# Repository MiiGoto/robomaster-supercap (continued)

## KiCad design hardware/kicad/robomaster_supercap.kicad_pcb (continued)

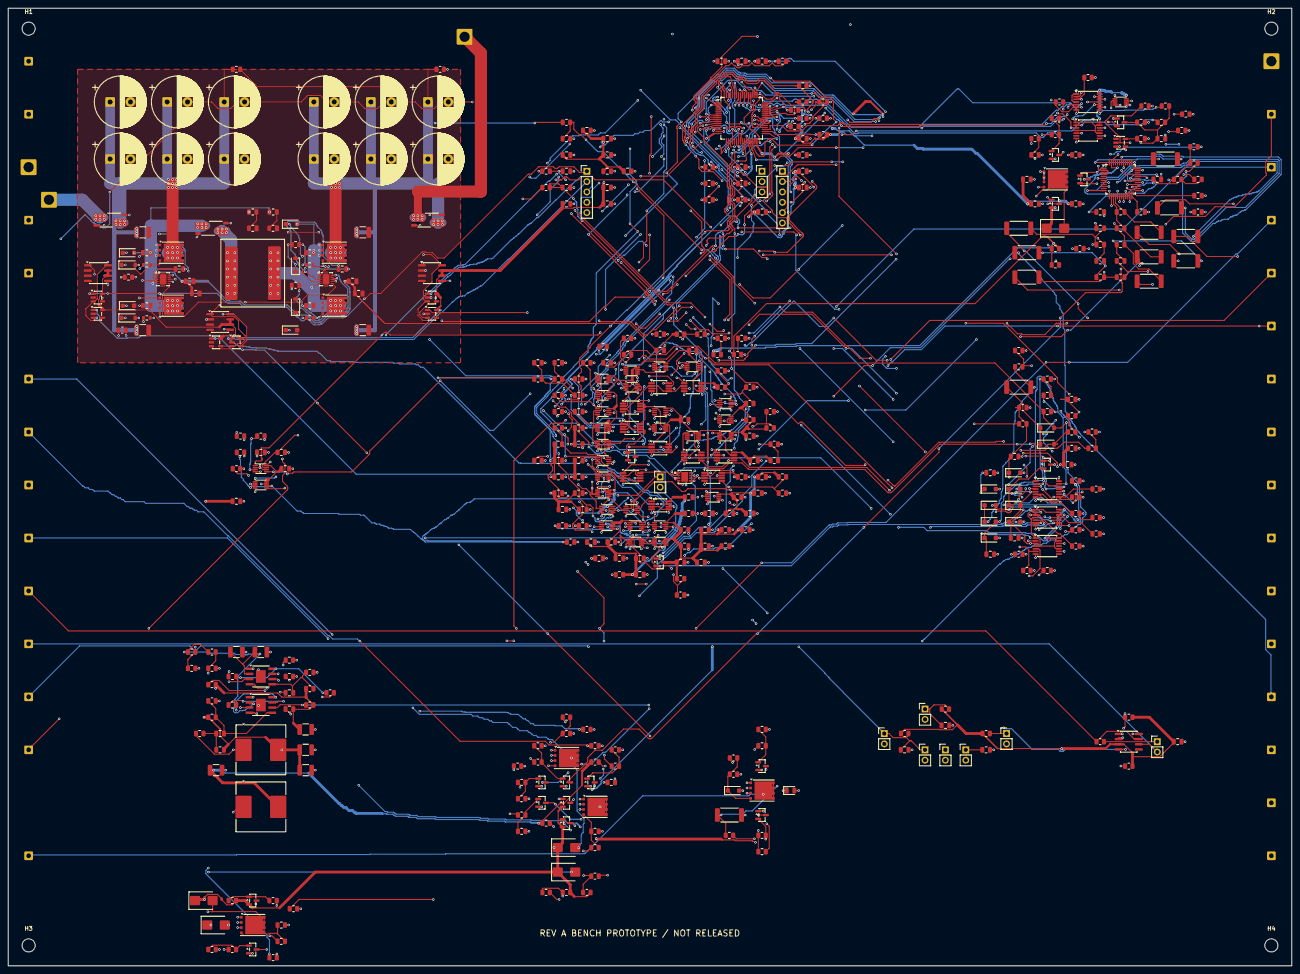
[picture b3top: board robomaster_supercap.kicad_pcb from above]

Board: 4 copper layers, 315.0 x 235.0 mm, 485 parts (0 on the bottom side), 285 nets.

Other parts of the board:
H1, H2, H3, H4: MountingHole_3.2mm_M3

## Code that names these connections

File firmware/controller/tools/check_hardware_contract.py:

"""Read-only audit against a native KiCad S-expression netlist export.

Usage: python -B check_hardware_contract.py path/to/rev_a.net
Export is local-only: it may contain private absolute paths and is not committed.
"""
import sys
from pathlib import Path

ROOT = Path(__file__).resolve().parents[3]
sys.path.insert(0, str(ROOT / "tools"))
from read_kicad import parse, child, children

# Physical LQFP64 pad, GPIO, electrical net; reviewed from U11 and datasheet.
CONTRACT = """
24 PB0 ARM_PULSE
25 PB1 WD_HEARTBEAT
26 PB2 MCU_GATE_REQUEST
30 PB10 PRE_BUS_REQUEST
33 PB11 BYP_BUS_REQUEST
38 PC6 BUS_ISO_REQUEST
39 PC7 CAP_ISO_REQUEST
40 PC8 PRE_CAP_REQUEST
41 PC9 BYP_CAP_REQUEST
52 PC10 DUMP_REQUEST
55 PD2 MON_CONFIG_VALID
42 PA8 PWM_AH
43 PA9 PWM_AL
44 PA10 PWM_BH
45 PA11 PWM_BL
46 PA12 HW_FAULT_N
8 PC0 TEMP_FET_ADC
9 PC1 TEMP_L_ADC
10 PC2 TEMP_BANK_ADC
11 PC3 BUS_RAW_ADC
12 PA0 BUS_V_ADC
13 PA1 CAP_V_ADC
18 PA4 BUS_I_ADC
19 PA5 CAP_I_ADC
20 PA6 IL_I_ADC
22 PC4 CAP_RAW_ADC
34 PB12 MON_CS_HOST
35 PB13 MON_SCLK_HOST
36 PB14 MON_MISO_HOST
37 PB15 MON_MOSI_HOST
53 PC11 MON_ALERT_HOST
61 PB8 CAN_RX
62 PB9 CAN_TX
54 PC12 CAN_STANDBY
14 PA2 UART_TX
17 PA3 UART_RX
49 PA13 SWDIO
50 PA14 SWCLK
56 PB3 SWO
2 PC13 PRE_CAP_FB
51 PA15 PRE_BUS_FB
57 PB4 BUS_ISO_FB
58 PB5 CAP_ISO_FB
59 PB6 BYP_BUS_FB
60 PB7 BYP_CAP_FB
23 PC5 REFEREE_PERMIT
7 PG10 NRST
"""

def check(path):
    native = parse(path.read_text(encoding="utf-8"))
    actual = {}
    for net in children(child(native, "nets"), "net"):
        for node in children(net, "node"):
            if child(node, "ref")[1] == "U11":
                actual[child(node, "pin")[1]] = (
                    child(node, "pinfunction")[1].split("_")[0], child(net, "name")[1])
    count = 0
    for row in CONTRACT.splitlines():
        if row.strip():
            pad, pin, name = row.split()
            assert actual.get(pad) == (pin, name), (pad, pin, name, actual.get(pad))
            count += 1
    board = (ROOT / "firmware/controller/Core/Src/board.c").read_text(encoding="utf-8")
    for token in ("GPIO_AF13_HRTIM1", "GPIO_AF5_SPI2", "GPIO_AF9_FDCAN1",
                  "ADC_CHANNEL_17", "ADC_CHANNEL_13", "ADC_REGULAR_RANK_6"):
        assert token in board, token
    print(f"PASS {count} U11 physical pin/net assignments; AF/ADC rank sentinels present")

if __name__ == "__main__":
    check(Path(sys.argv[1]))

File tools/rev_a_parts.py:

"""Original pin tables from manufacturer facts, not copied schematic assets.

Pin electrical types remain explicit for ERC. Package numbers are physical pad
numbers. Footprints are candidates; land dimensions require independent review.
"""
from dataclasses import dataclass

@dataclass
class Part:
    pins: dict
    footprint: str
    source: str = ''

P = {}
def part(name, pins, fp, source=''):
    # 'name:type'; omitted type is passive (R/C/L, contacts, semiconductor terminals).
    P[name] = Part({str(k): tuple(v.split(':')) if ':' in v else (v,'passive')
                    for k,v in pins.items()}, fp, source)

RFP='Resistor_SMD:R_0805_2012Metric'
CFP='Capacitor_SMD:C_0805_2012Metric'
SO8='Package_SO:SOIC-8_3.9x4.9mm_P1.27mm'
VSS8='Package_SO:VSSOP-8_3x3mm_P0.65mm'
DCU8='Package_SO:VSSOP-8_2.3x2mm_P0.5mm'
part('R',{1:'A',2:'B'},RFP)
part('J1_PAD',{1:'WIRE'},'Connector_Wire:SolderWire-0.5sqmm_1x01_D0.9mm_OD2.1mm')
part('C',{1:'A',2:'B'},CFP)
part('L',{1:'A',2:'B'},'Inductor_SMD:L_Coilcraft_XAL1510-223')
part('D',{1:'K',2:'A'},'Diode_SMD:D_SOD-123')
part('LED',{1:'K',2:'A'},'LED_SMD:LED_0805_2012Metric')
part('Q_NPN',{1:'B',2:'E',3:'C'},'Package_TO_SOT_SMD:SOT-23','https://www.nexperia.com/product/BC847B')
part('Q_PNP',{1:'B',2:'E',3:'C'},'Package_TO_SOT_SMD:SOT-23','https://www.nexperia.com/product/BC857B')
part('FUSE',{1:'A',2:'B'},'','https://www.littelfuse.com/assetdocs/littelfuse-datasheet-997-mini58v?assetguid=838cc4ad-f429-4185-a8e8-ccc70cd2b713')
# KiCad functional aliases: 1=S physical1/2/3, 2=G physical4,
# 3=D physical5/6/7/8 and drain metal. See pinout review before layout.
part('CSD18540Q5B',{1:'S_DS1_2_3',2:'G_DS4',3:'D_DS5_6_7_8'},
     'Package_SON:VSONP-8-1EP_5x6_P1.27mm','https://www.ti.com/lit/ds/symlink/csd18540q5b.pdf')
part('UCC27282DRCR',{1:'VDD:power_in',2:'NC:no_connect',3:'HB:passive',4:'HO:output',5:'HS:passive',6:'EN:input',7:'HI:input',8:'LI:input',9:'VSS:power_in',10:'LO:output',11:'EP:power_in'},
     'Package_SON:VSON-10-1EP_3x3mm_P0.5mm_EP1.65x2.4mm','https://www.ti.com/lit/ds/symlink/ucc27282.pdf')
for n in ('INA240A1D','INA240A2D'):
    part(n,{1:'INM:input',2:'GND:power_in',3:'REF2:input',4:'NC:no_connect',5:'OUT:output',6:'VS:power_in',7:'REF1:input',8:'INP:input'},SO8,'https://www.ti.com/lit/ds/symlink/ina240.pdf')
part('WSK25123L000FEA',{1:'I_P',2:'K_P',3:'K_M',4:'I_M'},
     'Resistor_SMD:R_Shunt_Vishay_WSK2512_6332Metric_T2.21mm','https://www.vishay.com/docs/30108/wsk2512.pdf')
part('INA293A1DBVR',{1:'OUT:output',2:'GND:power_in',3:'INP:input',4:'INM:input',5:'VS:power_in'},'Package_TO_SOT_SMD:SOT-23-5','https://www.ti.com/lit/ds/symlink/ina293.pdf')
part('INA301A1DGKR',{1:'VS:power_in',2:'OUT:output',3:'LIMIT:input',4:'GND:power_in',5:'RESET:input',6:'ALERT_N:open_collector',7:'INM:input',8:'INP:input'},VSS8,'https://www.ti.com/lit/ds/symlink/ina301.pdf')
part('TLV3202DGKR',{1:'OUT1:output',2:'INM1:input',3:'INP1:input',4:'GND:power_in',5:'INP2:input',6:'INM2:input',7:'OUT2:output',8:'VCC:power_in'},VSS8,'https://www.ti.com/lit/ds/symlink/tlv3202.pdf')
part('SN74LVC1G74DCUR',{1:'CLK:input',2:'D:input',3:'QN:output',4:'GND:power_in',5:'Q:output',6:'CLR_N:input',7:'PRE_N:input',8:'VCC:power_in'},DCU8,'https://www.ti.com/lit/ds/symlink/sn74lvc1g74.pdf')
part('SN74LVC2G08DCUR',{1:'A1:input',2:'B1:input',3:'Y2:output',4:'GND:power_in',5:'A2:input',6:'B2:input',7:'Y1:output',8:'VCC:power_in'},DCU8,'https://www.ti.com/lit/ds/symlink/sn74lvc2g08.pdf')
part('TPS3431SDRBR',{1:'VDD:power_in',2:'CWD:passive',3:'EN:input',4:'GND:power_in',5:'SET1:input',6:'WDI:input',7:'WDO_N:open_collector',8:'ENOUT:open_collector',9:'EP:power_in'},
     'Package_SON:VSON-8-1EP_3x3mm_P0.65mm_EP1.65x2.4mm','https://www.ti.com/lit/ds/symlink/tps3431.pdf')
part('TPS3839K33DBZR',{1:'GND:power_in',2:'RESET_N:output',3:'VDD:power_in'},'Package_TO_SOT_SMD:SOT-23','https://www.ti.com/lit/ds/symlink/tps3839.pdf')
part('LM5164DDAR',{1:'GND:power_in',2:'VIN:power_in',3:'EN:input',4:'RON:passive',5:'FB:input',6:'PGOOD:open_collector',7:'BST:passive',8:'SW:passive',9:'EP:power_in'},
     'Package_SO:TI_SO-PowerPAD-8','https://www.ti.com/lit/ds/symlink/lm5164.pdf')
part('TMUX1511PWR',{1:'SEL1:input',2:'S1:passive',3:'D1:passive',4:'SEL2:input',5:'S2:passive',6:'D2:passive',7:'GND:power_in',8:'D3:passive',9:'S3:passive',10:'SEL3:input',11:'D4:passive',12:'S4:passive',13:'SEL4:input',14:'VDD:power_in'},
     'Package_SO:TSSOP-14_4.4x5mm_P0.65mm','https://www.ti.com/lit/ds/symlink/tmux1511.pdf')
part('TLV431AIDBZR',{1:'REF:input',2:'K:passive',3:'A:passive'},'Package_TO_SOT_SMD:SOT-23','https://www.ti.com/lit/ds/symlink/tlv431.pdf')
part('SN65HVD230DR',{1:'D:input',2:'GND:power_in',3:'VCC:power_in',4:'R:output',5:'VREF:output',6:'CANL:bidirectional',7:'CANH:bidirectional',8:'RS:input'},SO8,'https://www.ti.com/lit/ds/symlink/sn65hvd230.pdf')
part('SN74LV1T34DBVR',{1:'NC:no_connect',2:'A:input',3:'GND:power_in',4:'Y:output',5:'VCC:power_in'},'Package_TO_SOT_SMD:SOT-23-5','https://www.ti.com/lit/ds/symlink/sn74lv1t34.pdf')
bq={1:'NC',2:'VC9',3:'NC',4:'VC8',5:'NC',6:'VC7',7:'NC',8:'VC6',9:'NC',10:'VC5',11:'NC',12:'VC4',13:'VC3',14:'VC2',15:'VC1',16:'VC0',17:'VSS:power_in',18:'SRP:input',19:'NC',20:'SRN:input',21:'TS1:passive',22:'TS2:passive',23:'TS3:passive',24:'REG18:power_out',25:'ALERT:open_collector',26:'SCLK:input',27:'MISO:output',28:'MOSI:input',29:'CS_N:input',30:'DFETOFF:input',31:'DCHG:output',32:'DDSG:output',33:'RST_SHUT:input',34:'REG2:power_out',35:'REG1:power_out',36:'REGIN:power_in',37:'BREG:output',38:'FUSE:passive',39:'PDSG:output',40:'PCHG:output',41:'LD:passive',42:'PACK:input',43:'DSG:output',44:'NC',45:'CHG:output',46:'CP1:passive',47:'BAT:power_in',48:'VC10:input'}
bq={i:('NC:no_connect' if s=='NC' else s+':input' if s.startswith('VC') and ':' not in s else s) for i,s in bq.items()}
part('BQ7694204PFBR',bq,'Package_QFP:TQFP-48_7x7mm_P0.5mm','https://www.ti.com/lit/ds/symlink/bq76942.pdf')
# LQFP64 physical pin map, DS12288 Rev6 Figure15 / Table12.
mcu_names='VBAT PC13 PC14 PC15 PF0 PF1 PG10 PC0 PC1 PC2 PC3 PA0 PA1 PA2 VSS VDD PA3 PA4 PA5 PA6 PA7 PC4 PC5 PB0 PB1 PB2 VSSA VREF+ VDDA PB10 VSS VDD PB11 PB12 PB13 PB14 PB15 PC6 PC7 PC8 PC9 PA8 PA9 PA10 PA11 PA12 VSS VDD PA13 PA14 PA15 PC10 PC11 PC12 PD2 PB3 PB4 PB5 PB6 PB7 PB8 PB9 VSS VDD'.split()
mcu=dict(enumerate(mcu_names,1))
part('STM32G474RET6',{i:s+(':power_in' if s in ('VBAT','VSS','VDD','VSSA','VDDA','VREF+') else ':bidirectional') for i,s in mcu.items()},
     'Package_QFP:LQFP-64_10x10mm_P0.5mm','https://www.st.com/resource/en/datasheet/stm32g474re.pdf')
for n in (2,3,4,5,6,10):
    part('J'+str(n),{i:'P'+str(i) for i in range(1,n+1)},f'Connector_PinHeader_2.54mm:PinHeader_1x{n:02}_P2.54mm_Vertical')
part('CONTACT',{1:'COM',2:'NO',3:'COIL_P',4:'COIL_M'},'','https://industry.panasonic.com/global/en/products/control/relay/vehicle/number/aev14012')
part('AQZ202G',{1:'LED_M',2:'LED_P',3:'ACDC_A',4:'ACDC_B'},'',
     'https://industry.panasonic.com/ac/cdn/e/control/relay/photomos/catalog/semi_eng_pwr1a_aqz10_20.pdf')
part('DDR60L12',{1:'VO_M',2:'VO_M',3:'VO_P',4:'VO_P',5:'VIN_P',6:'VIN_M'},'',
     'https://www.meanwell.com/Upload/PDF/DDR-60/DDR-60-SPEC.PDF')
part('DISCONNECT',{1:'COM',2:'SWITCHED'},'',
     'https://www.bluesea.com/products/compare/6004/6004200/6005200/6006/6006200')
part('PWR_FLAG',{1:'SUPPLY:power_out'},'')

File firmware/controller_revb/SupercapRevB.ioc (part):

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Mcu.Name=STM32G431C(6-8-B)Tx
Mcu.Package=LQFP48
Mcu.UserName=STM32G431CBTx
PA0.GPIOParameters=GPIO_Label
PA0.GPIO_Label=VNODE_S
PA0.Mode=IN1-Single-Ended
PA0.Signal=ADC1_IN1
PA1.GPIOParameters=GPIO_Label
PA1.GPIO_Label=VINC_S
PA1.Mode=IN2-Single-Ended
PA1.Signal=ADC1_IN2
PA11.Mode=FDCAN_Activate
PA11.Signal=FDCAN1_RX
PA12.Mode=FDCAN_Activate
PA12.Signal=FDCAN1_TX
PA13.Mode=Serial_Wire
PA13.Signal=SYS_JTMS-SWDIO
PA14.Mode=Serial_Wire
PA14.Signal=SYS_JTCK-SWCLK
PA2.GPIOParameters=GPIO_Label
PA2.GPIO_Label=TEMP_S
PA2.Mode=IN3-Single-Ended
PA2.Signal=ADC1_IN3
PA3.GPIOParameters=GPIO_Label
PA3.GPIO_Label=IIN_S
PA3.Mode=IN4-Single-Ended
PA3.Signal=ADC1_IN4
PA4.GPIOParameters=GPIO_Label
PA4.GPIO_Label=ILIM_DAC
PA4.Signal=COMP_DAC11_group
PA6.GPIOParameters=GPIO_Label
PA6.GPIO_Label=ICAP_S
PA6.Mode=IN3-Single-Ended
PA6.Signal=ADC2_IN3
PB0.GPIOParameters=PinState,GPIO_Label
PB0.GPIO_Label=EN_CHG
PB0.PinState=GPIO_PIN_RESET
PB0.Signal=GPIO_Output
PB1.GPIOParameters=PinState,GPIO_Label
PB1.GPIO_Label=EN_PMOS
PB1.PinState=GPIO_PIN_RESET
PB1.Signal=GPIO_Output
PB10.Mode=Asynchronous
PB10.Signal=USART3_TX
PB11.Mode=Asynchronous
PB11.Signal=USART3_RX
PB12.GPIOParameters=GPIO_Label
PB12.GPIO_Label=NODE_OK
PB12.Signal=GPIO_Input
PB13.GPIOParameters=GPIO_Label
PB13.GPIO_Label=PMOS_EN_RB
PB13.Signal=GPIO_Input
PB2.GPIOParameters=GPIO_Label
PB2.GPIO_Label=PGOOD
PB2.Signal=GPIO_Input
PB5.GPIOParameters=PinState,GPIO_Label
PB5.GPIO_Label=LED1
PB5.PinState=GPIO_PIN_RESET
PB5.Signal=GPIO_Output
PB6.GPIOParameters=PinState,GPIO_Label
PB6.GPIO_Label=LED2
PB6.PinState=GPIO_PIN_RESET
PB6.Signal=GPIO_Output
PF0-OSC_IN.Mode=HSE-External-Oscillator
PF0-OSC_IN.Signal=RCC_OSC_IN
PF1-OSC_OUT.Mode=HSE-External-Oscillator
PF1-OSC_OUT.Signal=RCC_OSC_OUT
RCC.HSE_VALUE=8000000
RCC.SYSCLKFreq_VALUE=170000000
RCC.SYSCLKSource=RCC_SYSCLKSOURCE_PLLCLK
board=custom
